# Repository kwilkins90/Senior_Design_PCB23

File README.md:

The files attached to this repo reflect the final iteration of the Data Capture Module. The PCB's final revision if RevF and the final revision for the packaging of the device is revision G.
There are several errors found on the PCB in this current iteration:
- The footprint for the display jack has pins that are incorrectly ordered.
- D1's belly pad should not be grounded.
- The Raspberry Pi was not correctly mirrored to the back of the PCB.

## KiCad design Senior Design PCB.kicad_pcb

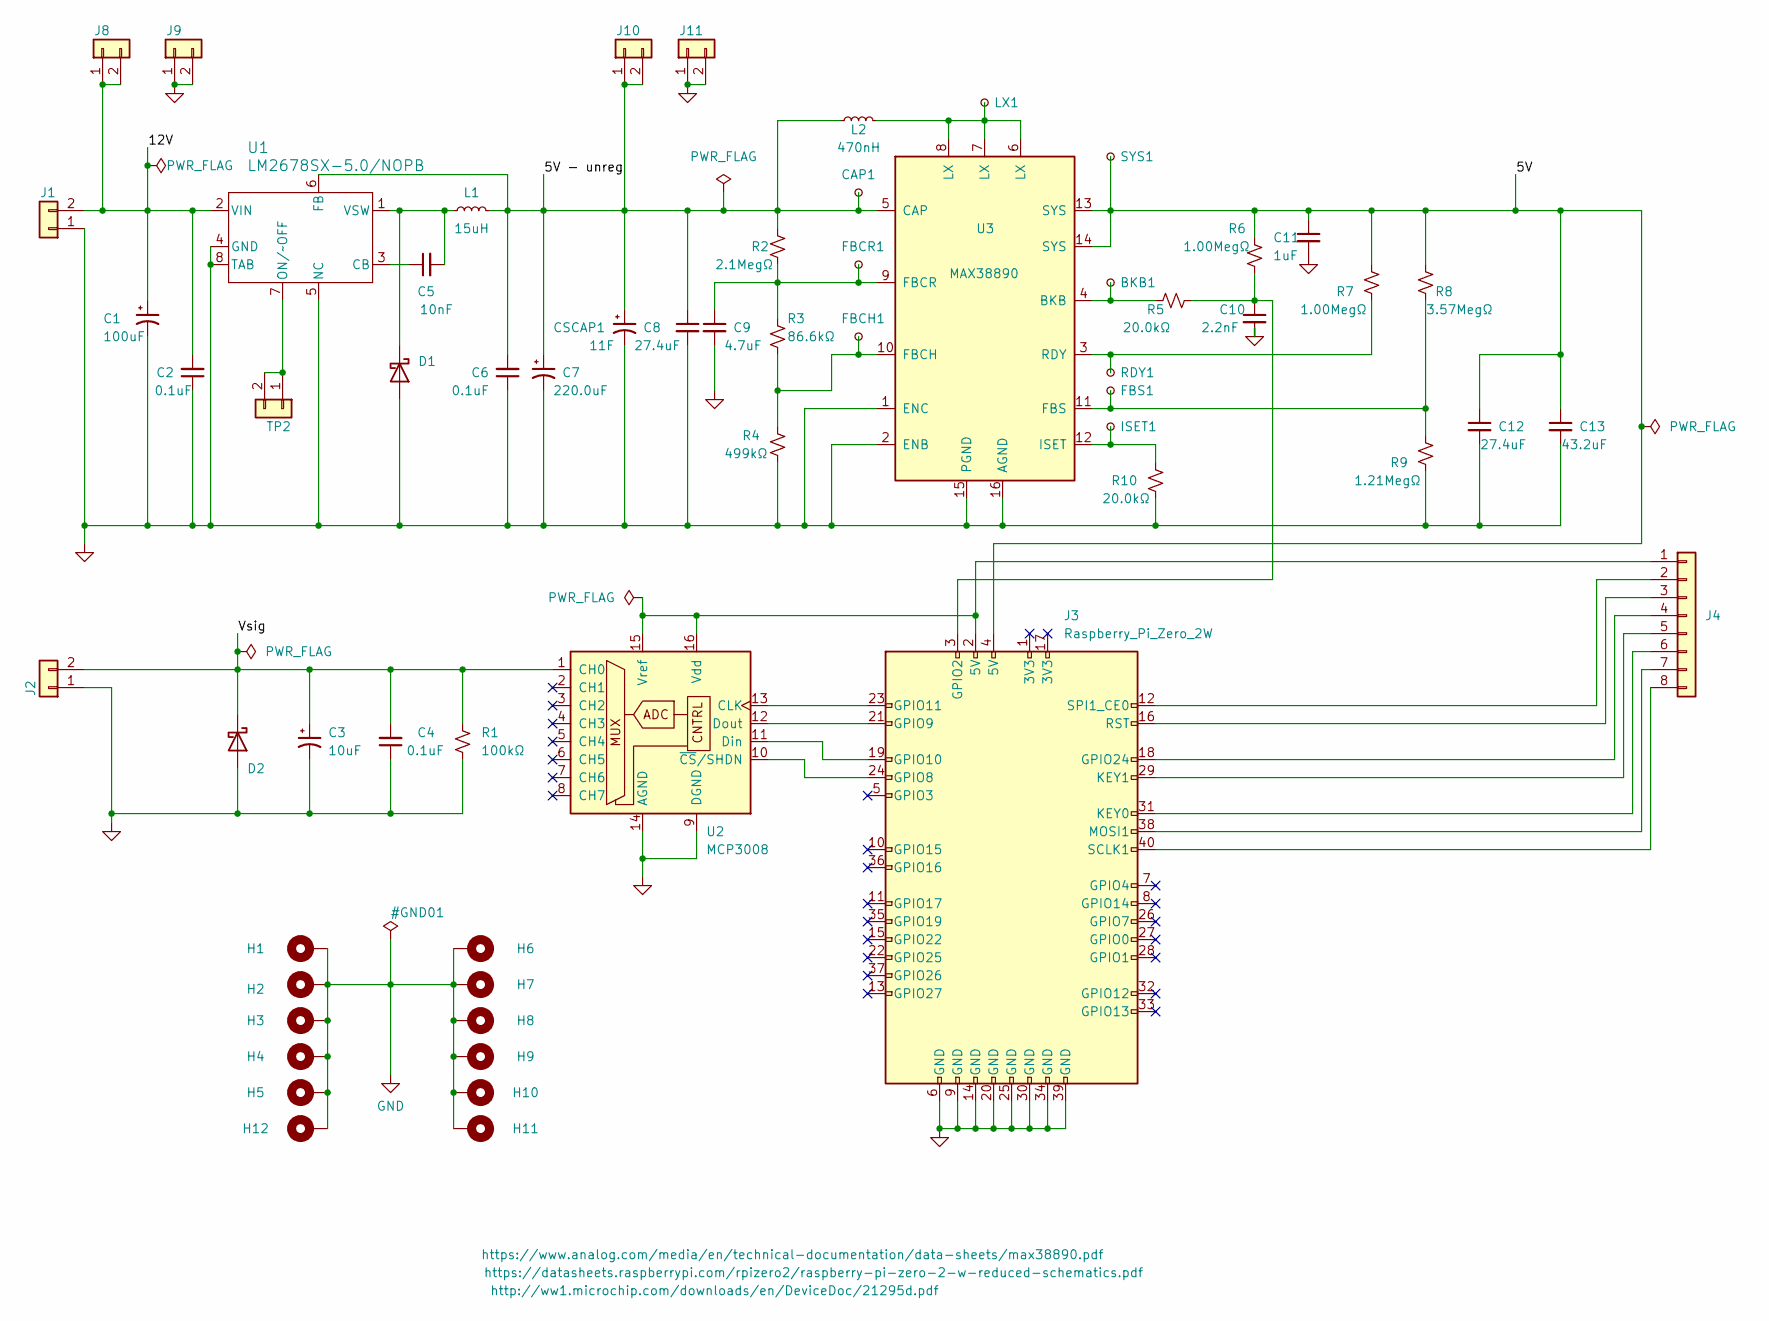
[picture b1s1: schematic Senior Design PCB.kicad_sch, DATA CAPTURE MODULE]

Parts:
BKB1: TestPoint_Small; TestPoint_Pad_D2.0mm
C1: 100uF; CP_Radial_D8.0mm_P2.50mm
C2, C6: 0.1uF; CP_Radial_D5.0mm_P2.50mm
C3: 10uF; CP_Radial_D5.0mm_P2.00mm
C4: 0.1uF; C_1206_3216Metric
C5: 10nF; CP_Radial_D10.0mm_P3.80mm
C7: 220.0uF; CP_Elec_8x6.9
C8, C12: 27.4uF; CAPC3216X180N
C9: 4.7uF; CAPC1608X87N
C10: 2.2nF; 0603
C11: 1uF; CAP_C0603_CND
C13: 43.2uF; CAPC3225X270N
CAP1: TestPoint_Small; TestPoint_Pad_D2.0mm
CSCAP1: 11F; CP_Radial_D10.0mm_P5.00mm
D1: 40V; D2PAK_STM
D2: 5.1V; D_DO-34_SOD68_P10.16mm_Horizontal
FBCH1: TestPoint_Small; TestPoint_Pad_D2.0mm
FBCR1: TestPoint_Small; TestPoint_Pad_D2.0mm
FBS1: TestPoint_Small; TestPoint_Pad_D2.0mm
H1, H2, H3, H4, H5, H6, H7, H8, H9, H10, H11, H12: MountingHole_Pad; MountingHole_3.2mm_M3_DIN965_Pad
ISET1: TestPoint_Small; TestPoint_Pad_D2.0mm
J1, J2, J8, J9, J10, J11: Conn_01x02; PinHeader_1x02_P2.54mm_Vertical
J3: Raspberry_Pi_Zero_2W; Raspberry_Pi_Zero_Socketed_THT_FaceDown_MountingHoles
J4: Conn_01x08; PinHeader_1x08_P2.54mm_Vertical
L1: 15uH; 15uHInductor
L2: 470nH; INDC2520X120N
LX1: TestPoint_Small; TestPoint_Pad_D2.0mm
R1: 100kΩ; R_Axial_DIN0207_L6.3mm_D2.5mm_P10.16mm_Horizontal
R2: 2.1MegΩ; RESC1508X50N
R3: 86.6kΩ; RES_ERJ3EKF4023V
R4: 499kΩ; RESC1508X50N
R5, R10: 20.0kΩ; RESC1508X50N
R6, R7: 1.00MegΩ; RESC1508X50N
R8: 3.57MegΩ; RESC1508X50N
R9: 1.21MegΩ; RESC1508X50N
RDY1: TestPoint_Small; TestPoint_Pad_D2.0mm
SYS1: TestPoint_Small; TestPoint_Pad_D2.0mm
TP2: Conn_01x02; PinHeader_1x02_P2.54mm_Vertical
U1: LM2678SX-5.0/NOPB; TS7B
U2: MCP3008; DIP-16_W7.62mm_LongPads
U3: MAX38890; TQFN-16-1EP_3x3mm_P0.5mm_EP1.23x1.23mm

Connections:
/5V: C11.1, C12.1, C13.1, J3.4 (5V), R6.1, R7.1, R8.1, SYS1.1, U3.13 (SYS), U3.14 (SYS)
/5V - unreg: C6.2, C7.1, C8.1, CAP1.1, CSCAP1.1, J10.1, J10.2, L1.2, L2.1, R2.1, U1.6 (FB), U3.5 (CAP)
/12V: C1.1, C2.2, J1.2, J8.1, J8.2, U1.2 (VIN)
/Vsig: C3.1, C4.2, D2.1 (K), J2.2, R1.1, U2.1 (CH0)
GND: C1.2, C2.1, C3.2, C4.1, C6.1, C7.2, C8.2, C9.2, C10.2, C11.2, C12.2, C13.2, CSCAP1.2, D1.2 (A), D1.3, D2.2 (A), H1.1, H2.1, H3.1, H4.1, H5.1, H6.1, H7.1, H8.1, H9.1, H10.1, H11.1, H12.1, J1.1, J2.1, J3.6 (GND), J3.9 (GND), J3.14 (GND), J3.20 (GND), J3.25 (GND), J3.30 (GND), J3.34 (GND), J3.39 (GND), J9.1, J9.2, J11.1, J11.2, L1.3, R1.2, R4.2, R9.2, R10.2, U1.4 (GND), U1.5 (NC), U1.8 (TAB), U2.9 (DGND), U2.14 (AGND), U3.1 (ENC), U3.2 (ENB), U3.15 (PGND), U3.16 (AGND), U3.17
unnamed: C5.2, D1.1 (K), L1.1, U1.1 (VSW)
unnamed: C10.1, J3.3 (GPIO2), R5.2, R6.2
unnamed: J3.24 (GPIO8), U2.10 (~CS/SHDN)
unnamed: J3.21 (GPIO9), U2.12 (Dout)
unnamed: J3.19 (GPIO10), U2.11 (Din)
unnamed: J3.23 (GPIO11), U2.13 (CLK)
unnamed: J3.18 (GPIO24), J4.4
unnamed: J3.31 (KEY0), J4.6
unnamed: J3.29 (KEY1), J4.5
unnamed: J3.38 (MOSI1), J4.7
unnamed: J3.16 (RST), J4.3
unnamed: J3.40 (SCLK1), J4.8
unnamed: J3.12 (SPI1_CE0), J4.2
unnamed: J3.2 (5V), J4.1, U2.15 (Vref), U2.16 (Vdd)
unnamed: L2.2, LX1.1, U3.6 (LX), U3.7 (LX), U3.8 (LX)
unnamed: TP2.1, TP2.2, U1.7 (ON/~OFF)
unnamed: C5.1, U1.3 (CB)
unnamed: BKB1.1, R5.1, U3.4 (BKB)
unnamed: FBCH1.1, R3.2, R4.1, U3.10 (FBCH)
unnamed: C9.1, FBCR1.1, R2.2, R3.1, U3.9 (FBCR)
unnamed: FBS1.1, R8.2, R9.1, U3.11 (FBS)
unnamed: ISET1.1, R10.1, U3.12 (ISET)
unnamed: R7.2, RDY1.1, U3.3 (RDY)

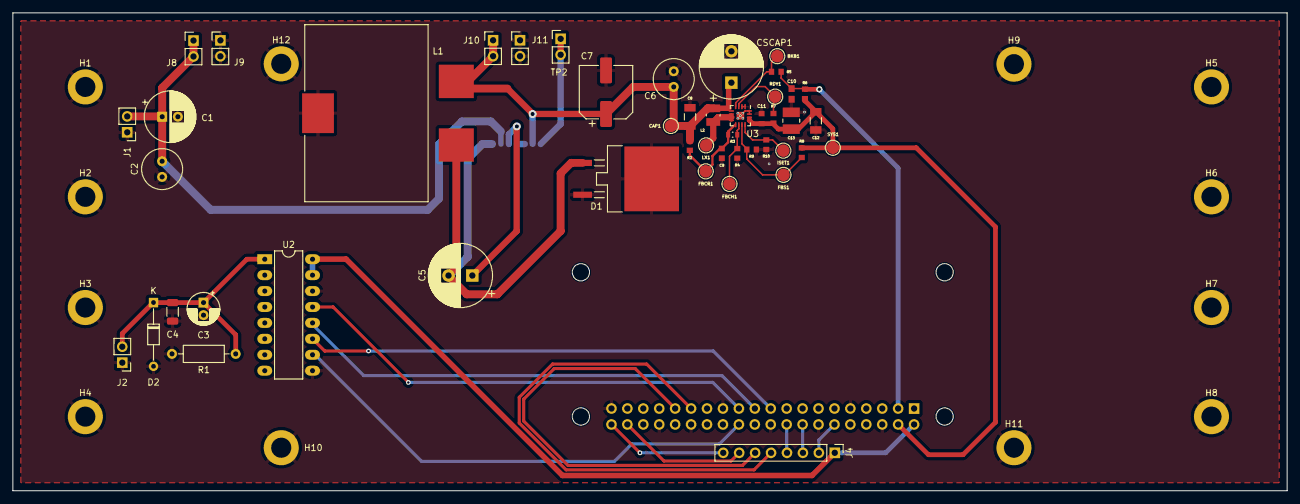
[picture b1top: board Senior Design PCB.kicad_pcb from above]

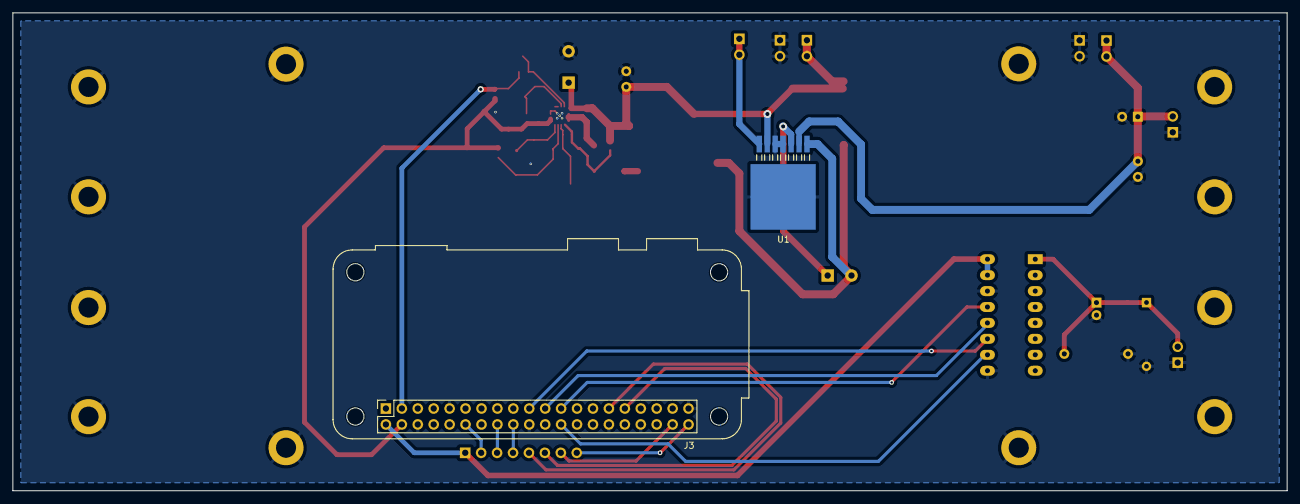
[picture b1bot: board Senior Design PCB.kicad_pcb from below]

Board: 2 copper layers, 203.2 x 76.2 mm, 61 parts (2 on the bottom side), 28 nets.

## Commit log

2023-11-05 More footprints added.
2023-11-09 All footprints added.
2023-11-09 Fixed a few footprints. Started the design process. I'll start making branches after today.
2023-11-11 Laid second draft of traces. No ground plane has been added.
2023-11-12 Laid fourth draft of traces and passed all drc checks. gnd planes added and the mounting holes are added, as well. Remaining steps are to add leds or 50k ohm resistor.
2023-11-20 Mark Bruno edits implemented.
2023-12-11 Final files added to 'most recent files' branch.
2023-12-14 Final files added and SolidWorks files.
